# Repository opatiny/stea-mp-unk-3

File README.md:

# stea-mp-unk-3
## Building an mp3 player in a steampunk style
The goal of this project is to build an autonomous mp3 player contained in an old leather suitcase. It works on batteries, has a 32 characters led display (home-made) and offers an oldschool way to chose the music to play: it uses perforated PCBs with a unique connectivity.

## Results
You can see the final player on this video (in french):
[https://youtu.be/DE0FV9JWbVA](https://youtu.be/DE0FV9JWbVA)

## Documentation
Sadly, the documentation to this project is written in french.
You can find a two-parts description of the project on the following links:

__Frist part: developing and producing the PCBs__

[https://oci.gyre.ch/blog/?post/2018/02/01/18H-patiny](https://oci.gyre.ch/blog/?post/2018/02/01/18H-patiny)

__Second part: finishing the project__

[https://oci.gyre.ch/blog/?post/2017/12/04/18P-patiny](https://oci.gyre.ch/blog/?post/2017/12/04/18P-patiny)

## Programming
All the code related to this project can be found [here](https://github.com/opatiny/node-steam-player).

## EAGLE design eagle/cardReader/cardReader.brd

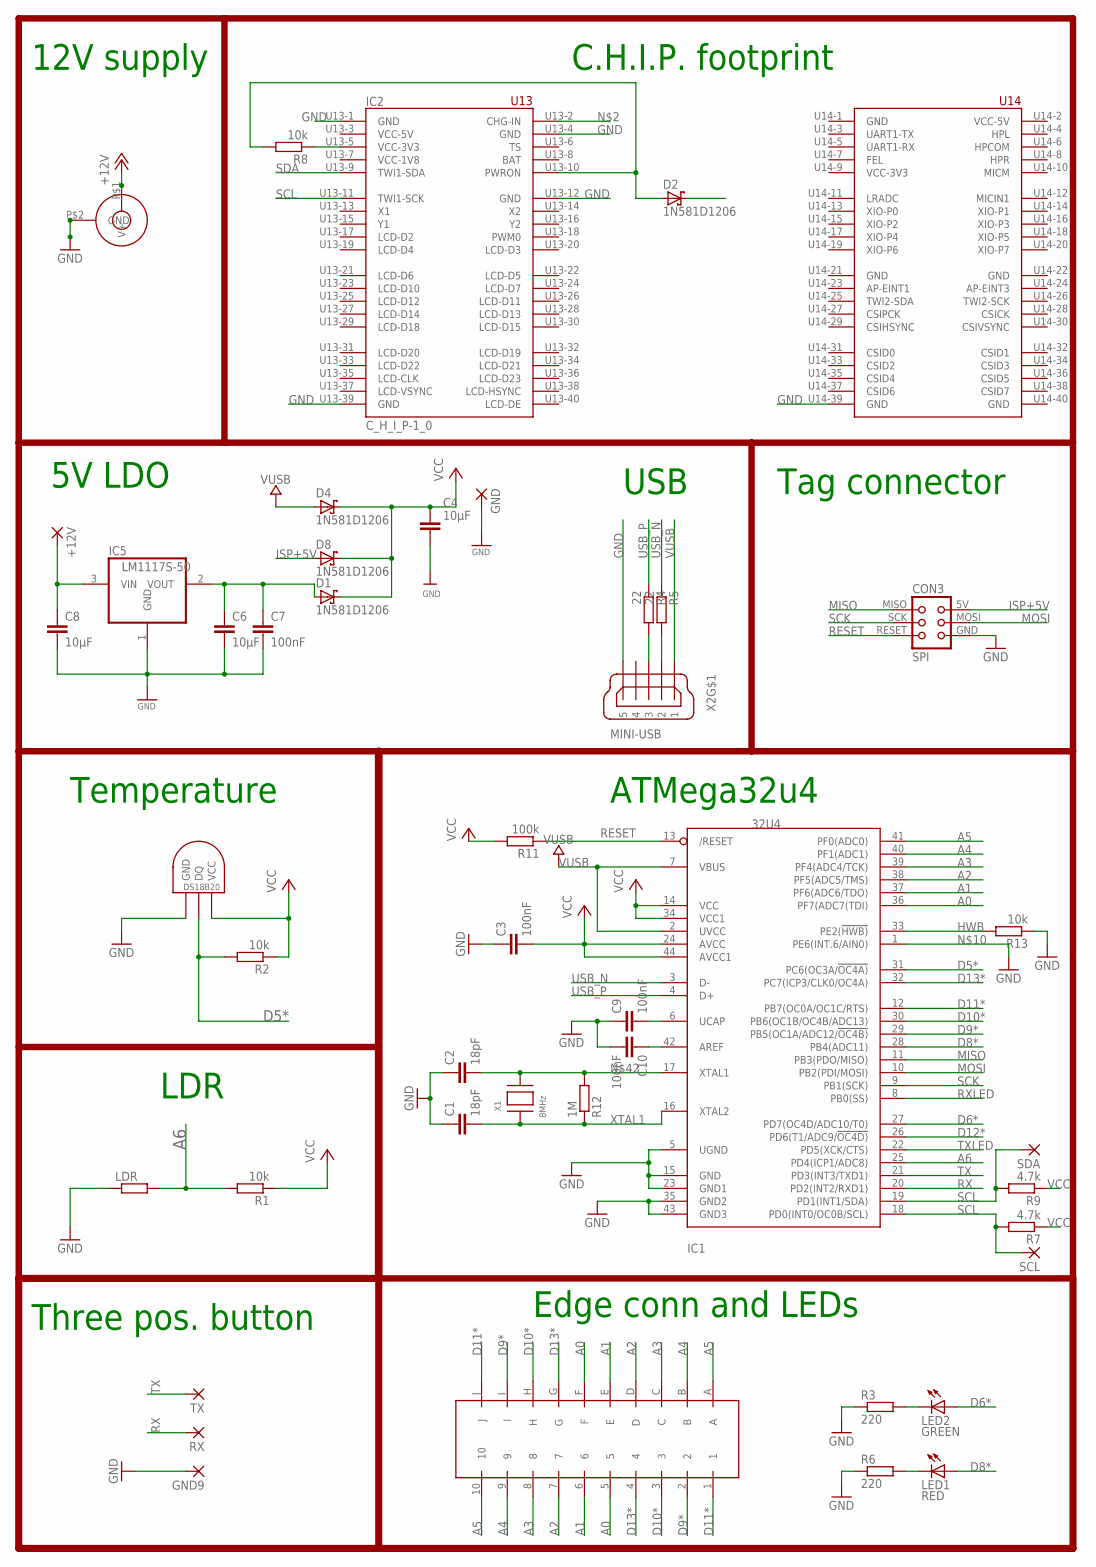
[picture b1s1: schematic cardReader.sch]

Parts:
+12V: SMD5; SMD2,54-5,08
C1, C2: 18pF; C0805K; MPN 77-VJ1206A180JXXPBC; LCSC C1797
C3, C7, C9, C10: 100nF; C0805K; MPN 80-C1206C104K5R; LCSC C49678
C4: 10µF; C1206
C6, C8: 10µF; C0805K; MPN 77-VJ1206V106ZXQTBC; LCSC C15850
CON2: JACK_DC_BARREL; DC_BARREL
CON3: SPI; TC2030-MCP-NL
D1, D2, D4, D8: 1N581D1206; LED-1206
GND, GND9: SMD5; SMD2,54-5,08
IC1: 32U4; TQFP44; MPN 556-ATMEGA32U4RC-AU; LCSC C44854
IC2: C_H_I_P-1_0
IC5: LM1117S-50; SOT223; LCSC C126027
LDR: R-EU_0207/2V; 0207/2V
LED1: RED; LED5MM
LED2: GREEN; LED5MM
R1, R2, R8: 10k; R0805; MPN RC1206FR-07100KL; LCSC C17407
R3, R6: 220; 0204/7
R4, R5: 22; R0805; LCSC C17561
R7, R9: 4.7k; R0805; MPN RC1206FR-07100KL; LCSC C17407
R11: 100k; R0805; MPN RC1206FR-07100KL; LCSC C17407
R12: 1M; R0805; LCSC C17514
R13: 10k; R0805; LCSC C17414
RX: SMD5; SMD2,54-5,08
SCL: SMD5; SMD2,54-5,08
SDA: SMD5; SMD2,54-5,08
TX: SMD5; SMD2,54-5,08
U$1: DS1820TO92; DS1820
U$3: CONN2X10PRINT
X1: 8MHz; NX6035; MPN 729-F60800010; LCSC C122522
X2: MINI-USB; 32005-201; MPN 649-10033526-N3212LF; LCSC C46391

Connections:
+12V: +12V.1, C8.1, CON2.P$1 (V+), IC5.3 (VIN)
A0: IC1.36 (PF7(ADC7(TDI)), U$3.5, U$3.F
A1: IC1.37 (PF6(ADC6/TDO)), U$3.6, U$3.E
A2: IC1.38 (PF5(ADC5/TMS)), U$3.7, U$3.D
A3: IC1.39 (PF4(ADC4/TCK)), U$3.8, U$3.C
A4: IC1.40 (PF1(ADC1)), U$3.9, U$3.B
A5: IC1.41 (PF0(ADC0)), U$3.10, U$3.A
A6: IC1.25 (PD4(ICP1/ADC8)), LDR.2, R1.2
AREF: C10.1, IC1.42 (AREF)
BAT: IC2.U13-8 (BAT)
D5*: IC1.31 (PC6(OC3A/!OC4A)), R2.2, U$1.DQ
D6*: IC1.27 (PD7(OC4D/ADC10/T0)), LED2.A
D8*: IC1.28 (PB4(ADC11)), LED1.A
D9*: IC1.29 (PB5(OC1A/ADC12/!OC4B)), U$3.2, U$3.I
D10*: IC1.30 (PB6(OC1B/OC4B/ADC13)), U$3.3, U$3.H
D11*: IC1.12 (PB7(OC0A/OC1C/RTS)), U$3.1, U$3.J
D12*: IC1.26 (PD6(T1/ADC9/!OC4D))
D13*: IC1.32 (PC7(ICP3/CLK0/OC4A)), U$3.4, U$3.G
GND: C1.1, C2.1, C3.1, C4.2, C6.2, C7.2, C8.2, C9.1, C10.2, CON2.P$2 (GND), CON3.GND, GND.1, GND9.1, IC1.5 (UGND), IC1.15 (GND), IC1.23 (GND1), IC1.35 (GND2), IC1.43 (GND3), IC2.U13-1 (GND), IC2.U13-4 (GND), IC2.U13-12 (GND), IC2.U13-39 (GND), IC2.U14-1 (GND), IC2.U14-21 (GND), IC2.U14-22 (GND), IC2.U14-39 (GND), IC2.U14-40 (GND), IC5.1 (GND), LDR.1, R3.1, R6.1, R13.1, U$1.GND, X2.5
HWB: IC1.33 (PE2(!HWB)), R13.2
ISP+5V: CON3.5V (VCC), D8.A
MISO: CON3.MISO, IC1.11 (PB3(PDO/MISO))
MOSI: CON3.MOSI, IC1.10 (PB2(PDI/MOSI))
unnamed: C9.2, IC1.6 (UCAP)
unnamed: LED2.K (C), R3.2
unnamed: LED1.K (C), R6.2
unnamed: C6.1, C7.1, D1.A, IC5.2 (VOUT)
unnamed: D2.C, IC1.1 (PE6(INT.6/AIN0))
unnamed: C2.2, IC1.17 (XTAL1), R12.2, X1.P$2
PWRON: D2.A, IC2.U13-10 (PWRON), R8.2
RESET: CON3.RESET, IC1.13 (/RESET), R11.1
RX: IC1.20 (PD2(INT2/RXD1)), RX.1
RXLED: IC1.8 (PB0(SS))
SCK: CON3.SCK, IC1.9 (PB1(SCK))
SCL: IC1.18 (PD0(INT0/OC0B/SCL)), IC2.U13-11 (TWI1-SCK), R7.2, SCL.1
SDA: IC1.19 (PD1(INT1/SDA)), IC2.U13-9 (TWI1-SDA), R9.2, SDA.1
TX: IC1.21 (PD3(INT3/TXD1)), TX.1
TXLED: IC1.22 (PD5(XCK/CTS))
USBC_N: R5.2, X2.2
USBC_P: R4.2, X2.3
USB_N: IC1.3 (D-), R5.1
USB_P: IC1.4 (D+), R4.1
VCC: C3.2, C4.1, D1.C, D4.C, D8.C, IC1.14 (VCC), IC1.24 (AVCC), IC1.34 (VCC1), IC1.44 (AVCC1), R1.1, R2.1, R7.1, R9.1, R11.2, U$1.VDD (VCC)
VCC-3V3@1: IC2.U13-5 (VCC-3V3), R8.1
VUSB: D4.A, IC1.2 (UVCC), IC1.7 (VBUS), X2.1
XTAL1: C1.2, IC1.16 (XTAL2), R12.1, X1.P$1

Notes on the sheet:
USB
ATMega32u4
5V LDO
Temperature
Tag connector
LDR
Three pos. button
Edge conn and LEDs
12V supply
C.H.I.P. footprint

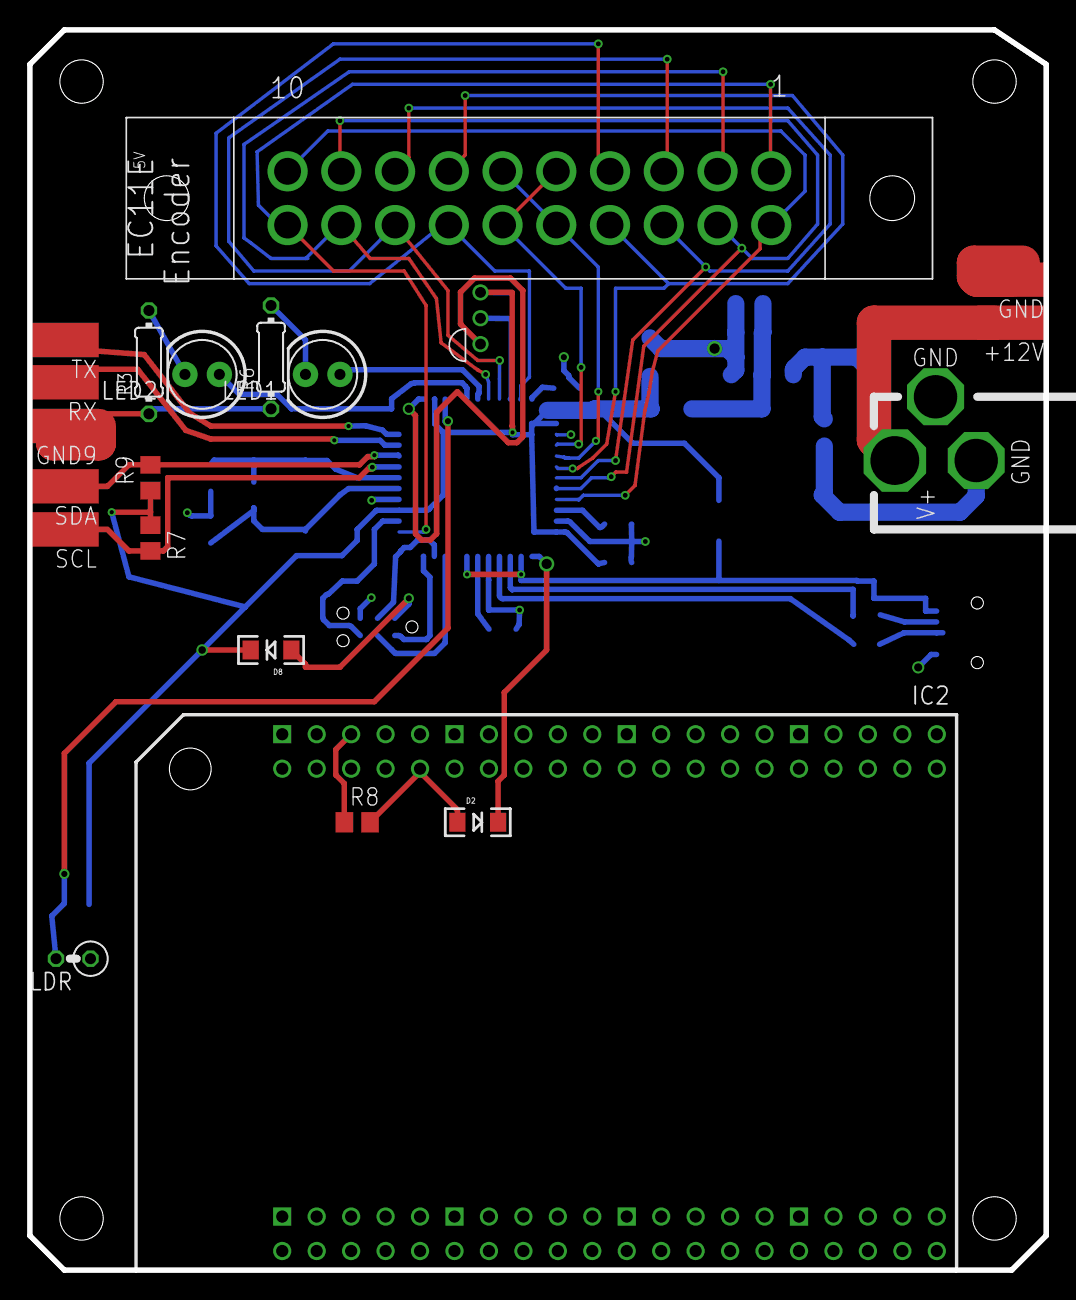
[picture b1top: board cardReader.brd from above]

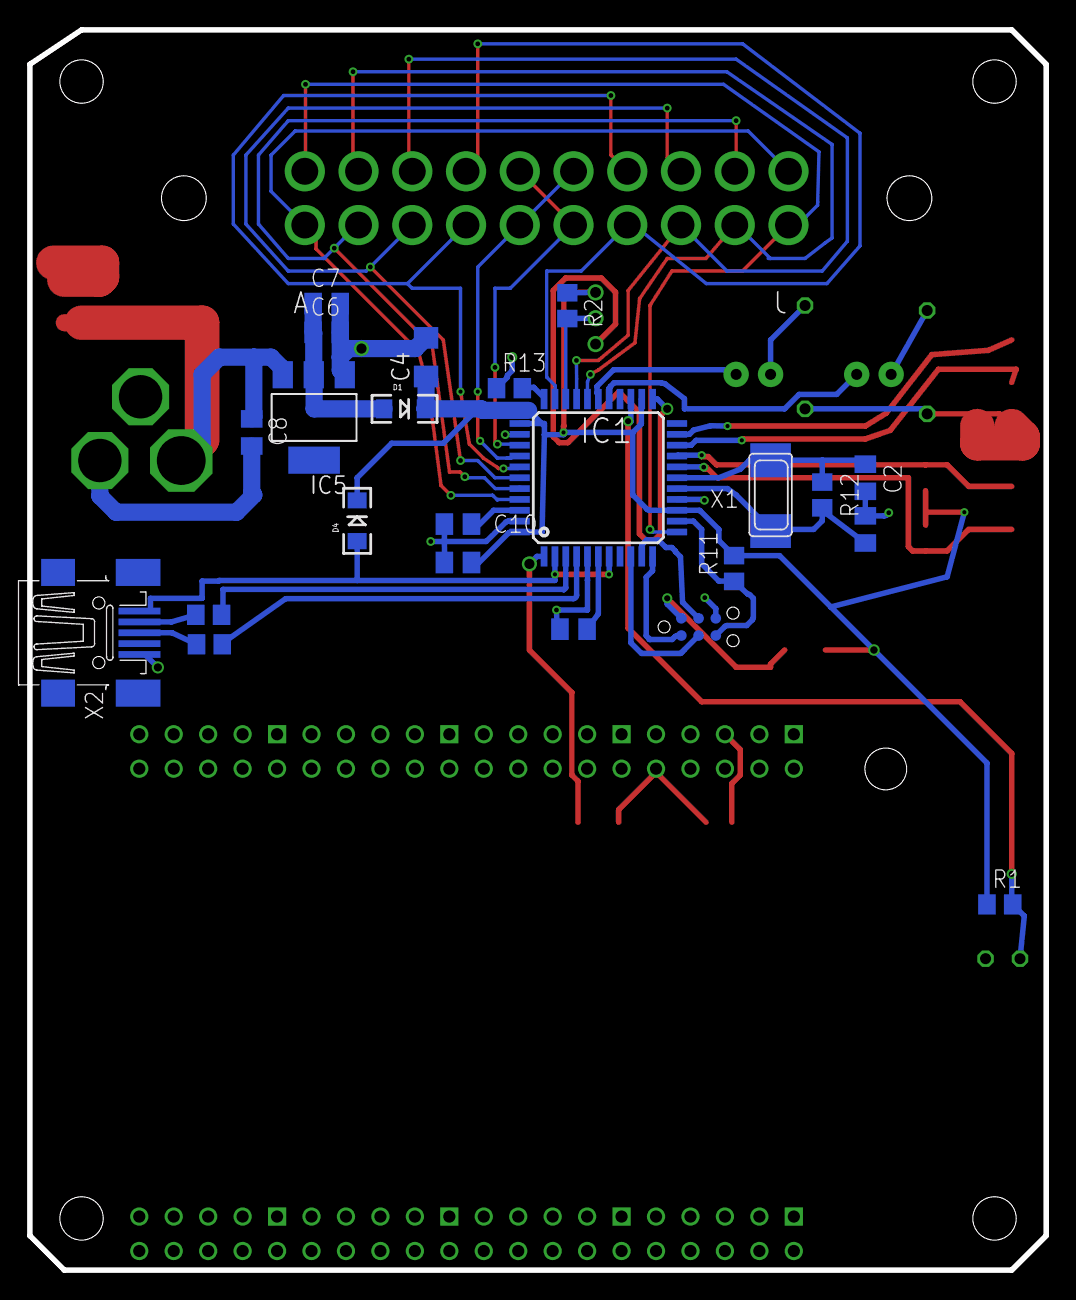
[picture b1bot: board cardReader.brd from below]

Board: 4 copper layers, 74.9 x 91.4 mm, 44 parts (23 on the bottom side), 42 nets.

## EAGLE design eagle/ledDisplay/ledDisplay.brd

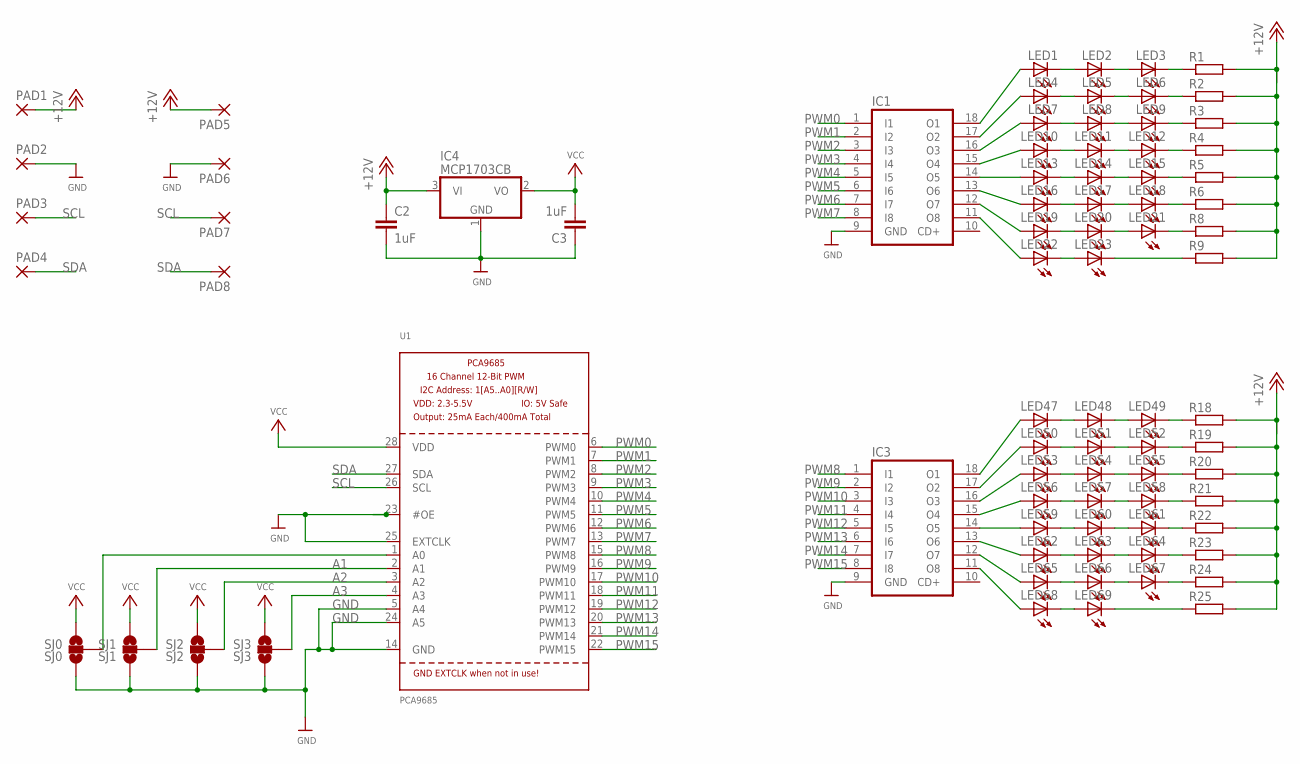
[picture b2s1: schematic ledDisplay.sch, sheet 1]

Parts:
C2, C3: 1uF; C1206
IC1: ULN2803A; SO18W
IC3: ULN2803AIC; DIL18
IC4: MCP1703CB; SOT23
LED1, LED2, LED3, LED4, LED5, LED6, LED7, LED8, LED9, LED10, LED11, LED12, LED13, LED14, LED15, LED16, LED17, LED18, LED19, LED20, LED21, LED22, LED23, LED47, LED48, LED49, LED50, LED51, LED52, LED53, LED54, LED55, LED56, LED57, LED58, LED59, LED60, LED61, LED62, LED63, LED64, LED65, LED66, LED67, LED68, LED69: LED5MM
PAD1, PAD2, PAD3, PAD4, PAD5, PAD6, PAD7, PAD8: SMD5; SMD2,54-5,08
R1, R2, R3, R4, R5, R6, R8, R9, R18, R19, R20, R21, R22, R23, R24, R25: R-EU_0204/7; 0204/7
SJ0: SJ0; SJ_3
SJ1: SJ1; SJ_3
SJ2: SJ2; SJ_3
SJ3: SJ3; SJ_3
U1: PCA9685; TSSOP28

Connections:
+12V: C2.1, IC4.3 (VI), PAD1.1, PAD5.1, R1.2, R2.2, R3.2, R4.2, R5.2, R6.2, R8.2, R9.2, R18.2, R19.2, R20.2, R21.2, R22.2, R23.2, R24.2, R25.2
A1: SJ1.2, U1.2 (A1)
A2: SJ2.2, U1.3 (A2)
A3: SJ3.2, U1.4 (A3)
GND: C2.2, C3.1, IC1.9 (GND), IC3.9 (GND), IC4.1 (GND), PAD2.1, PAD6.1, SJ0.1, SJ1.1, SJ2.1, SJ3.1, U1.5 (A4), U1.14 (GND), U1.23 (#OE), U1.24 (A5), U1.25 (EXTCLK)
unnamed: LED1.K (C), LED2.A
unnamed: LED2.K (C), LED3.A
unnamed: IC1.18 (O1), LED1.A
unnamed: LED3.K (C), R1.1
unnamed: LED7.K (C), LED8.A
unnamed: LED4.K (C), LED5.A
unnamed: LED5.K (C), LED6.A
unnamed: IC1.17 (O2), LED4.A
unnamed: LED6.K (C), R2.1
unnamed: LED13.K (C), LED14.A
unnamed: LED8.K (C), LED9.A
unnamed: LED9.K (C), R3.1
unnamed: LED14.K (C), LED15.A
unnamed: LED10.K (C), LED11.A
unnamed: LED11.K (C), LED12.A
unnamed: LED12.K (C), R4.1
unnamed: LED15.K (C), R5.1
unnamed: IC1.16 (O3), LED7.A
unnamed: IC1.15 (O4), LED10.A
unnamed: IC1.14 (O5), LED13.A
unnamed: LED16.K (C), LED17.A
unnamed: LED17.K (C), LED18.A
unnamed: LED18.K (C), R6.1
unnamed: IC1.13 (O6), LED16.A
unnamed: LED19.K (C), LED20.A
unnamed: LED20.K (C), LED21.A
unnamed: LED21.K (C), R8.1
unnamed: IC1.12 (O7), LED19.A
unnamed: LED22.K (C), LED23.A
unnamed: LED23.K (C), R9.1
unnamed: IC1.11 (O8), LED22.A
unnamed: LED47.K (C), LED48.A
unnamed: SJ0.2, U1.1 (A0)
unnamed: LED48.K (C), LED49.A
unnamed: IC3.18 (O1), LED47.A
unnamed: LED49.K (C), R18.1
unnamed: LED50.K (C), LED51.A
unnamed: LED51.K (C), LED52.A
unnamed: IC3.17 (O2), LED50.A
unnamed: LED52.K (C), R19.1
unnamed: LED53.K (C), LED54.A
unnamed: LED54.K (C), LED55.A
unnamed: LED55.K (C), R20.1
unnamed: LED56.K (C), LED57.A
unnamed: LED57.K (C), LED58.A
unnamed: LED58.K (C), R21.1
unnamed: IC3.16 (O3), LED53.A
unnamed: IC3.15 (O4), LED56.A
unnamed: LED59.K (C), LED60.A
unnamed: LED60.K (C), LED61.A
unnamed: LED61.K (C), R22.1
unnamed: LED62.K (C), LED63.A
unnamed: LED63.K (C), LED64.A
unnamed: LED64.K (C), R23.1
unnamed: IC3.14 (O5), LED59.A
unnamed: IC3.13 (O6), LED62.A
unnamed: LED65.K (C), LED66.A
unnamed: LED66.K (C), LED67.A
unnamed: LED67.K (C), R24.1
unnamed: LED68.K (C), LED69.A
unnamed: IC3.12 (O7), LED65.A
unnamed: IC3.11 (O8), LED68.A
unnamed: LED69.K (C), R25.1
PWM0: IC1.1 (I1), U1.6 (PWM0)
PWM1: IC1.2 (I2), U1.7 (PWM1)
PWM2: IC1.3 (I3), U1.8 (PWM2)
PWM3: IC1.4 (I4), U1.9 (PWM3)
PWM4: IC1.5 (I5), U1.10 (PWM4)
PWM5: IC1.6 (I6), U1.11 (PWM5)
PWM6: IC1.7 (I7), U1.12 (PWM6)
PWM7: IC1.8 (I8), U1.13 (PWM7)
PWM8: IC3.1 (I1), U1.15 (PWM8)
PWM9: IC3.2 (I2), U1.16 (PWM9)
PWM10: IC3.3 (I3), U1.17 (PWM10)
PWM11: IC3.4 (I4), U1.18 (PWM11)
PWM12: IC3.5 (I5), U1.19 (PWM12)
PWM13: IC3.6 (I6), U1.20 (PWM13)
PWM14: IC3.7 (I7), U1.21 (PWM14)
PWM15: IC3.8 (I8), U1.22 (PWM15)
SCL: PAD3.1, PAD7.1, U1.26 (SCL)
SDA: PAD4.1, PAD8.1, U1.27 (SDA)
VCC: C3.2, IC4.2 (VO), SJ0.3, SJ1.3, SJ2.3, SJ3.3, U1.28 (VDD)

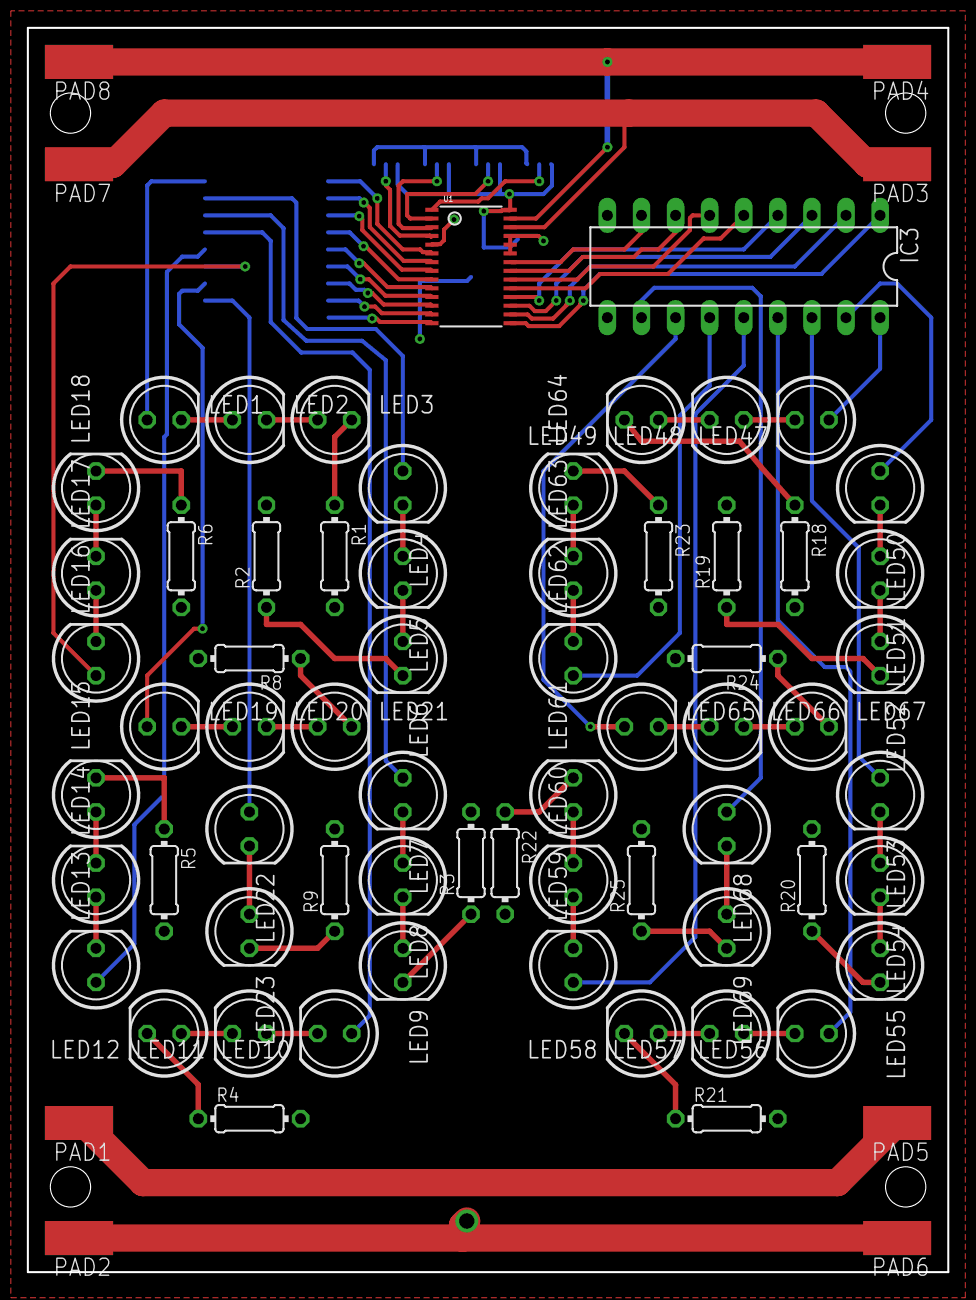
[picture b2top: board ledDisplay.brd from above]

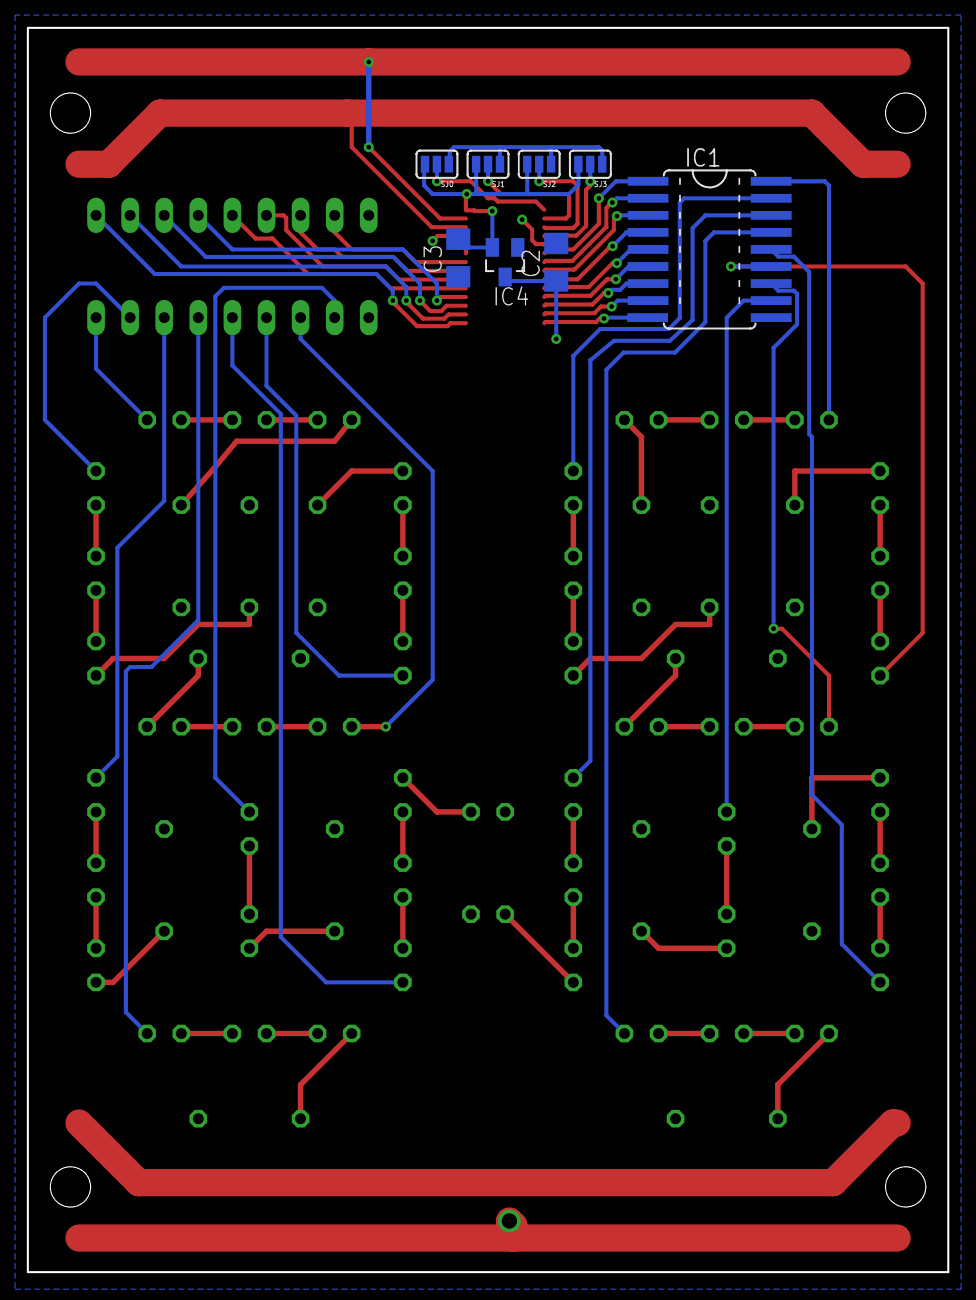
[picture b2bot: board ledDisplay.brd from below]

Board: 2 copper layers, 68.6 x 92.7 mm, 80 parts (8 on the bottom side), 87 nets.

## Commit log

2017-12-27 v. 1.0 of led display board and docs folder
2017-12-31 add arduino files to test led display pcb
2017-12-31 work on freecad files
2018-01-01 add v. 1.0 of perfCard
2018-03-17 hole git (feat): synced github with school server
2018-04-08 feat (arduino): i2c_scanner changed
2018-04-08 feat (arduino): minor changes in cardScan and cardScanWithLed
2018-04-08 add the required arduino libraries
2018-04-08 add cardreader mt
2018-04-08 move cardReaderMT and add i2c slave
2018-04-09 feat (arduino): add multiThread and work on cardReaderMT
2018-04-10 feat (arduino): add comments to cardReaderMT
2018-04-10 fix (freecad): commit problems and add loudspeakerSupport
2018-04-11 feat (arduino): comments to cardReaderMT and add buttontest and squaresOnMatrix2
2018-04-11 add (freecad): loudspeakerSupport.dxf
2018-04-11 feat (arduino): work on button interaction
2018-04-13 feat (arduino): work on ledDisplay
2018-04-13 feat (arduino): add button thread to cardReaderMT
2018-04-13 add gold and platinium card
2018-04-13 fix blinking and delay
2018-04-15 fix parameter name and byte order for card ID
2018-04-18 feat (arduino): add testWakeUp
2018-04-18 add (blog): add index.wiki, work on intro
2018-04-18 feat (blog)
2018-04-18 feat (blog): minor changes
2018-04-21 feat (blog): work on methodes and split files by section
2018-04-21 feat (blog): work on methodes
2018-04-22 feat (eagle): update perfCard and add cam processor
2018-04-28 feat (arduino/cardReader): add animation for rainbow card
2018-04-28 feat (arduino/cardReaderMT): fix rainbow animation
2018-04-28 feat (blog): work on methodes and introduction
2018-05-01 add picture
2018-05-10 feat (arduino): modify ledDisplay tests
2018-05-11 add (cardeader)
2018-05-11 feat (blog): enhance materiel and methodes
2018-05-12 feat (arduino): fix button thread for CHIP shutdown
2018-05-12 fix buttons
2018-05-13 feat (blog): work on methodes, resultats and materiel
2018-05-13 feat (blog): change files extention to .txt
2018-05-13 feat (arduino): remove space
2018-05-13 feat (blog): make all links clickable and work on methodes
2018-05-14 feat (blog): finishing up
2018-05-15 feat (blog): last modifications

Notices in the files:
parts and their libraries:
lpatiny: ©2009 ROFA.cz - modified and updated by Robert Darlington ‹rdarlington@gmail.com›
SparkFun: Licensing: CC v3.0 Share-Alike You are welcome to use this library for commercial purposes.
